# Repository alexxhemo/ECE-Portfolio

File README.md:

# Engineering Portfolio — Alexander Xhemo

This repository contains a collection of my engineering and software projects across hardware design, embedded systems, VLSI, C/C++/Python development, Linux systems programming, and full-stack web development.

The goal of this portfolio is to show the range of projects I have worked on, including circuit design, PCB layout, microcontroller programming, digital/VLSI design, backend/frontend development, and algorithmic software projects.

---

## Portfolio Areas

### PCB Design

This section includes PCB design projects involving schematic capture, component selection, board layout, routing, and manufacturing outputs.

Projects include:

- Optical transceiver PCB
- Audio amplifier PCB
- Schematic and layout documentation
- Gerber/manufacturing files where applicable
- Design screenshots and project notes

Tools used:

- Altium Designer
- KiCad
- Circuit simulation tools
- PCB layout and routing workflows

Large generated simulation files, such as `.raw` files, are intentionally excluded from the repository to keep the project clean and lightweight.

---

### VLSI Layouts and Schematics

This section contains VLSI design work, including transistor-level schematics, layouts, and timing analysis.

Projects include:

- Static master-slave register
- Full adder schematic and layout
- Sequential arithmetic circuit integration
- DRC and LVS verification work
- Setup time, hold time, and clock-to-Q delay analysis

Tools and concepts used:

- Cadence Virtuoso
- CMOS transistor-level design
- Layout design with shared diffusion
- DRC/LVS debugging
- Timing measurements and waveform analysis

---

### Microcontroller Embedded C

This section includes embedded C projects developed for microcontroller-based systems.

Projects include:

- Microcontroller I/O control
- UART/USART communication
- SPI and I2C peripheral communication
- ADC and DAC usage
- PWM control
- RTC-based timing
- State-machine-based embedded logic

Tools and platforms used:

- Microchip Studio
- AVR microcontrollers
- Embedded C
- Oscilloscope and hardware debugging
- Serial communication debugging

---

### Linear Regression Visualizer

This project is a C++ and Python-based linear regression visualizer used to demonstrate regression modeling, error calculation, and data visualization.

Main features:

- Linear regression model calculation
- Visualization of regression line and data points
- Error metric calculation
- Clean project structure for experimenting with regression behavior
- Backend logic for handling model calculations

Languages and tools used:

- C++
- Python
- Data visualization libraries
- Object-oriented programming concepts

---

### CPU Scheduler for Ubuntu

This project implements a CPU scheduling calculator and simulator for Linux/Ubuntu.

Implemented scheduling algorithms include:

- First-Come, First-Served
- Shortest Job First
- Round Robin
- Priority Scheduling

The project calculates and displays scheduling metrics such as:

- Waiting time
- Turnaround time
- Completion time
- Average performance metrics

Tools and concepts used:

- C/C++
- Ubuntu/Linux environment
- Process scheduling concepts
- Command-line compilation and testing

---

### Full-Stack Web Applications

This section includes two full-stack web applications involving frontend development, backend/API integration, authentication, database interaction, and team collaboration.

Project work includes:

- Frontend page development
- Responsive user interface design
- Backend API integration
- User authentication flows
- Database-backed application logic
- Team collaboration using GitHub, Trello, and Discord

Technologies used across these projects include:

- React
- JavaScript
- Flask / backend APIs
- SQLite
- AWS Lambda
- Auth0
- GitHub Actions / CI workflows
- Docker

---

## Skills Demonstrated

This portfolio demonstrates experience in:

- PCB schematic capture and board layout
- VLSI schematic and physical layout design
- Embedded C programming
- Microcontroller peripheral configuration
- C++ and Python application development
- Linux-based development
- CPU scheduling algorithms
- Full-stack web application development
- Git and GitHub version control
- Debugging hardware, software, and integration issues
- Technical documentation and project organization

---

## Repository Organization

The repository is organized by project category:

```text
ECE-Portfolio/
│
├── PCB Design/
│   ├── Optical Transceiver/
│   └── Audio Amplifier/
│
├── VLSI/
│   ├── Layouts/
│   ├── Schematics/
│   └── Timing Analysis/
│
├── Microcontroller Embedded C/
│
├── Linear Regression Visualizer/
│
├── CPU Scheduler Ubuntu/
│
├── Full Stack Web Apps/
│
└── README.md

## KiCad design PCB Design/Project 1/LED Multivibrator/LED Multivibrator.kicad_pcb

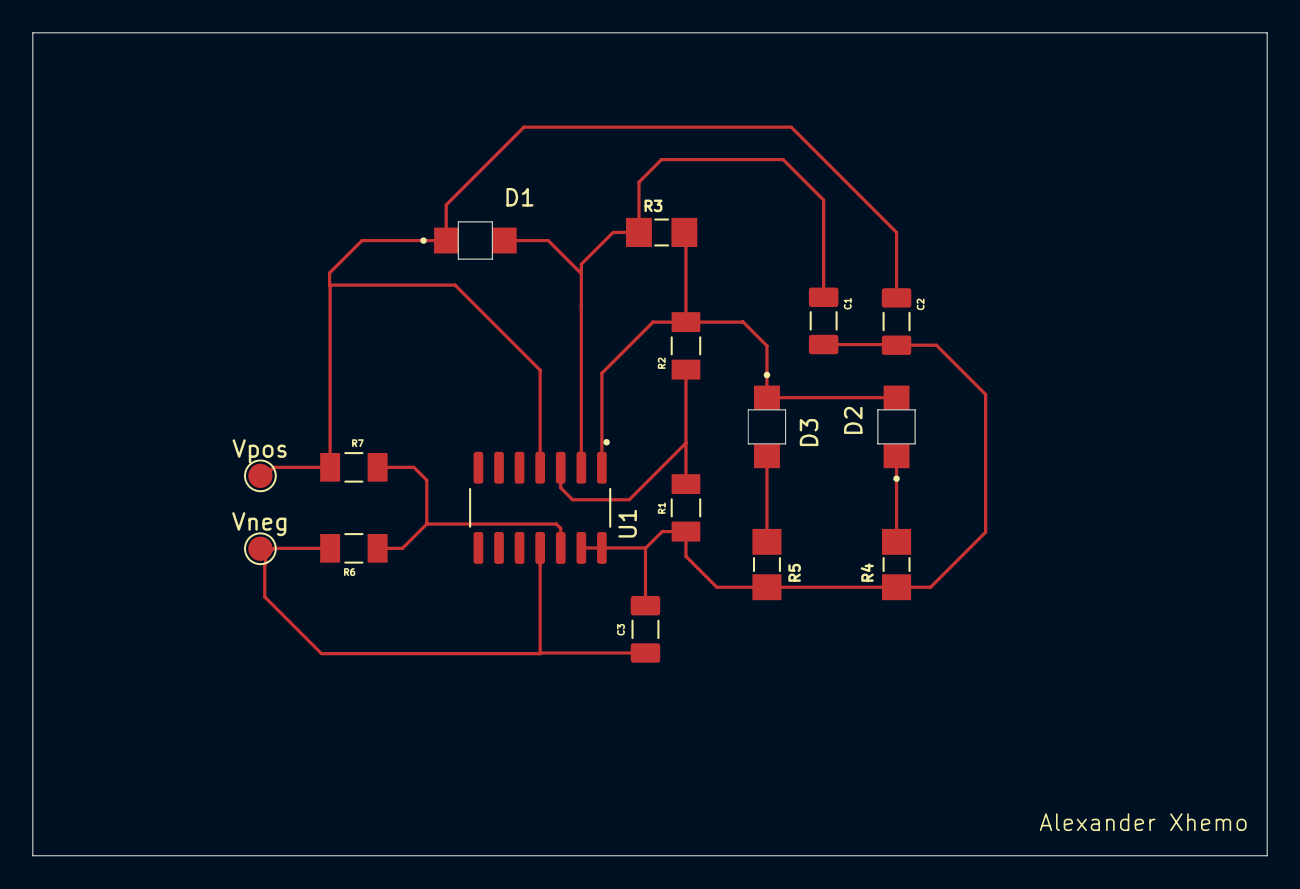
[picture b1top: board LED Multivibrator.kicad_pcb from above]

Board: 2 copper layers, 76.2 x 50.8 mm, 16 parts (0 on the bottom side), 9 nets.

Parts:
C1, C2, C3: CL31B106KAHNNNE; CAPC3216X180N
D1, D2, D3: LTST-C230KRKT; LED_LTST-C230KRKT
R1, R2, R6, R7: 1k; RESC3216X70N
R3: 20k; RESC3216X65
R4, R5: 330; RESC3216X65
U1: LM324DR; SOIC127P600X175-14N
Vneg: TestPoint; TestPoint_Pad_D1.5mm
Vpos: TestPoint; TestPoint_Pad_D1.5mm

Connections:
+4.5: C2.1, D1.C, R7.1, U1.4 (VCC), Vpos.1
-4.5V: C3.1, R6.2, U1.11 (GND), Vneg.1
GND: C1.2, C2.2, C3.2, R1.1, R4.2, R5.2, U1.13 (4IN-), U1.14 (4OUT)
unnamed: D2.C, R4.1
unnamed: D3.A, R5.1
unnamed: R1.2, R2.1, U1.3 (1IN+)
unnamed: C1.1, D1.A, R3.1, U1.2 (1IN-)
unnamed: D2.A, D3.C, R2.2, R3.2, U1.1 (1OUT)
unnamed: R6.1, R7.2, U1.12 (4IN+)

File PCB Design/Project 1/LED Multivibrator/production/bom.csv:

Designator,Footprint,Quantity,Value,LCSC Part #
"C1, C2, C3",CAPC3216X180N,3,CL31B106KAHNNNE,
"D1, D2, D3",LED_LTST-C230KRKT,3,LTST-C230KRKT,
"R1, R2, R6, R7",RESC3216X70N,4,1k,
R3,RESC3216X65,1,20k,
"R4, R5",RESC3216X65,2,330,
U1,SOIC127P600X175-14N,1,LM324DR,
"VNEG, VPOS",TestPoint_Pad_D1.5mm,2,TestPoint,

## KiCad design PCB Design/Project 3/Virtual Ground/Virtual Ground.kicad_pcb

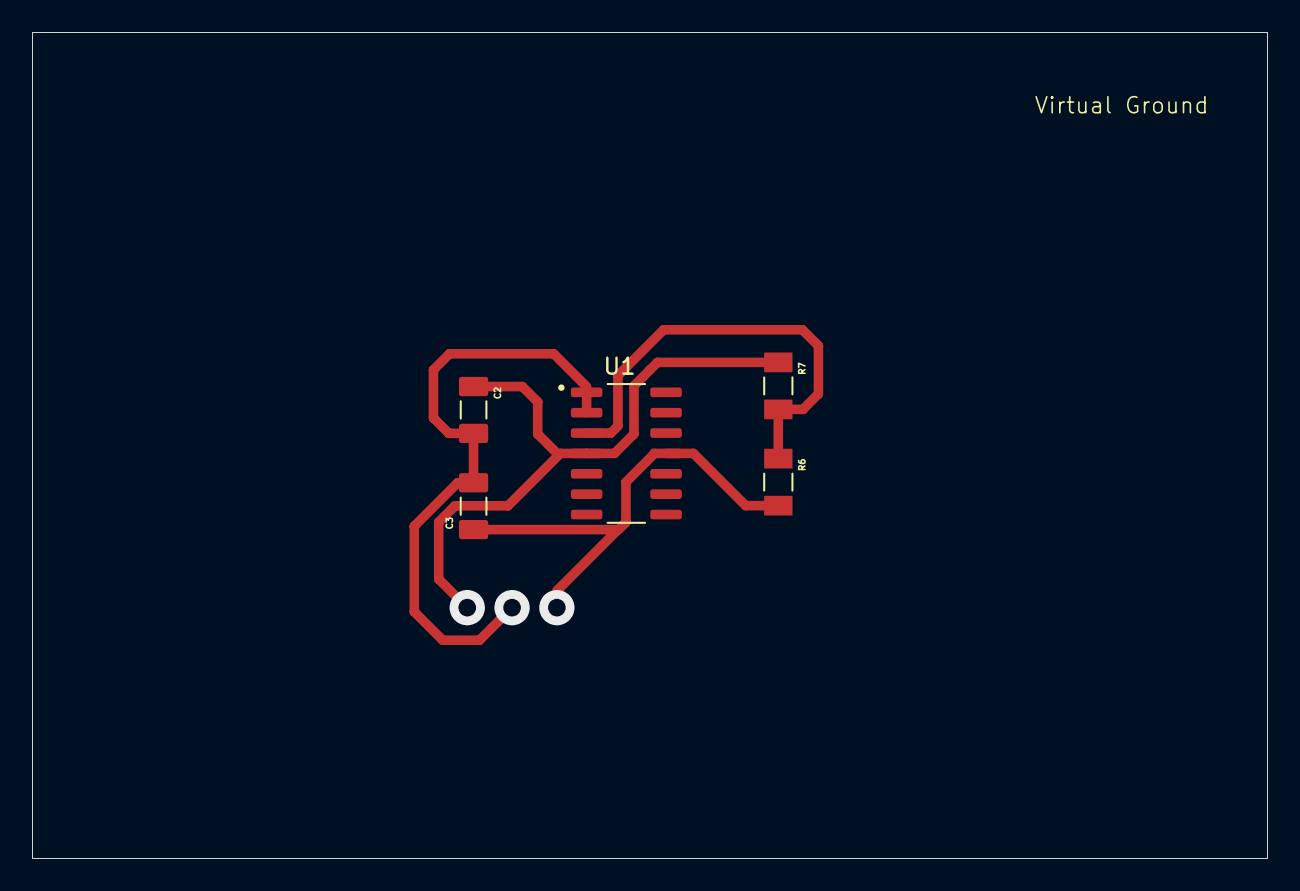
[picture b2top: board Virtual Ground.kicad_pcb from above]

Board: 2 copper layers, 77.0 x 51.5 mm, 5 parts (0 on the bottom side), 4 nets.

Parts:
C2, C3: CL31B106KAHNNNE; CAPC3216X180N
R6, R7: 1k; RESC3216X70N
U1: LM324DR; SOIC127P600X175-14N

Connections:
/V+: C2.1, R7.1, U1.4 (VCC)
/V-: C3.1, R6.2, U1.11 (GND)
/Virtual_Ground: C2.2, C3.2, U1.1 (1OUT), U1.2 (1IN-)
unnamed: R6.1, R7.2, U1.3 (1IN+)

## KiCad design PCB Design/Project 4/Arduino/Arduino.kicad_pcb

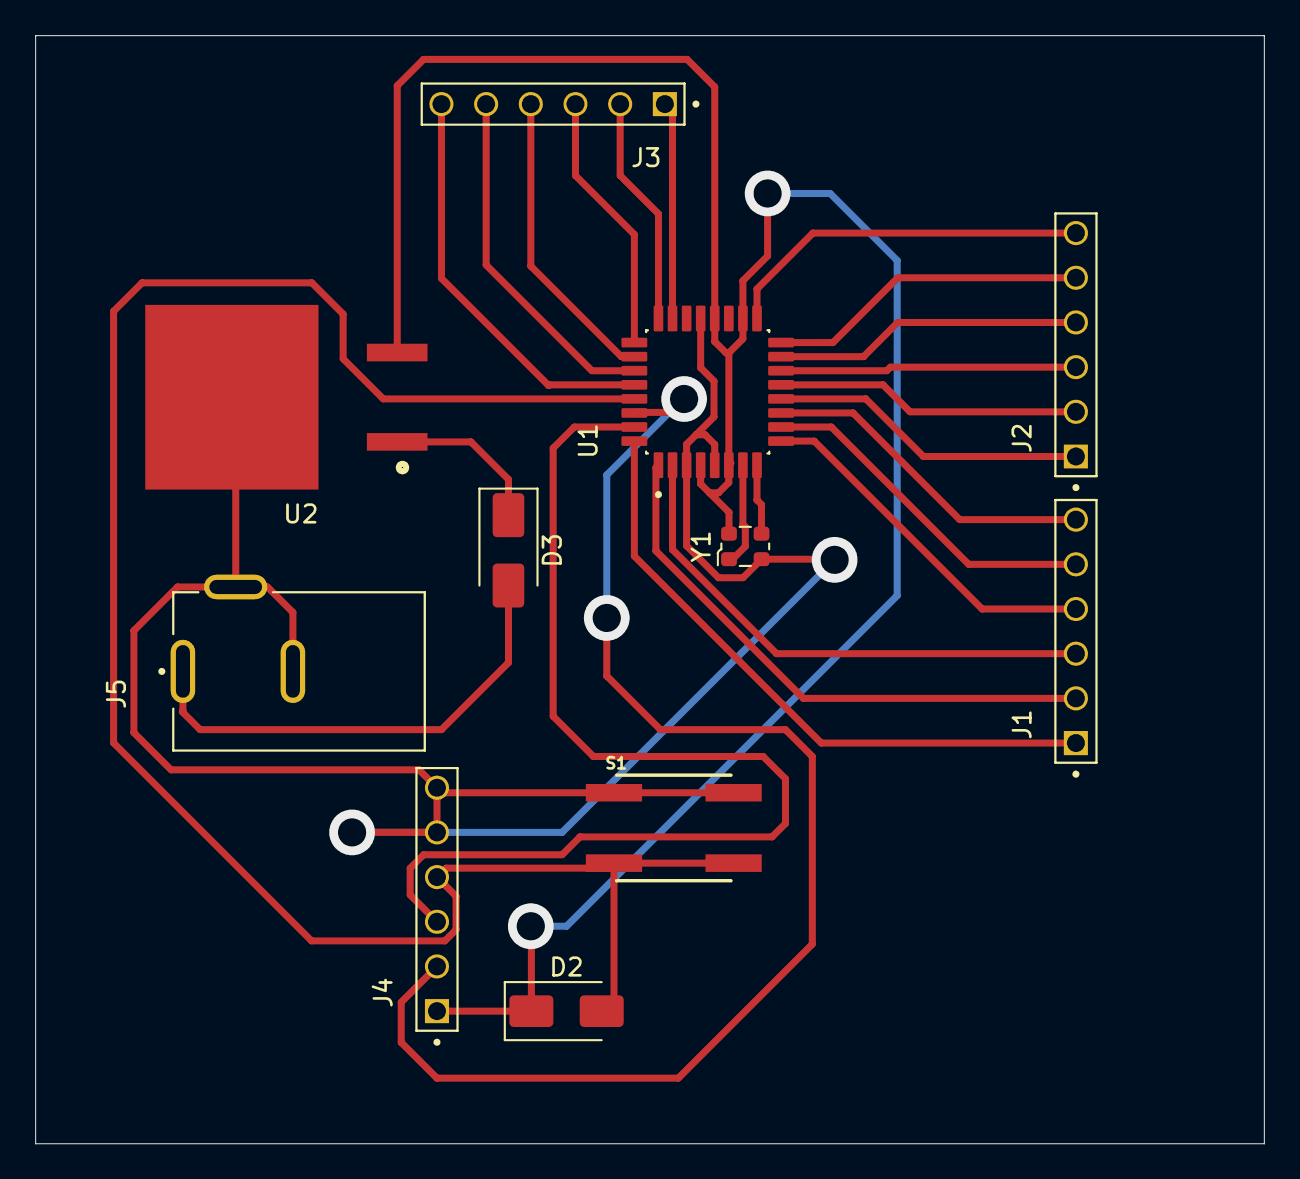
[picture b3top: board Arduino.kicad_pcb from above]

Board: 2 copper layers, 69.8 x 63.0 mm, 11 parts (0 on the bottom side), 27 nets.

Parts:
D2, D3: MRA4007T3G; D_SMA
J1, J2, J3, J4: 3-644456-6; TE_3-644456-6
J5: 54-00166; TENSILITY_54-00166
S1: EVQ-Q2B02W; SW_EVQ-Q2B02W
U1: ATMEGA328P-AU; QFP80P900X900X120-32N
U2: L7805ACD2T-TR; TO254P1515X470-3N
Y1: ECS-2520MV-xxx-xx; Oscillator_SMD_ECS_2520MV-xxx-xx-4Pin_2.5x2.0mm

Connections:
/LED: J2.6, U1.17 (PB5)
/MISO: J2.5, U1.16 (PB4)
/MOSI: J2.4, U1.15 (PB3)
/PB0: J2.1, U1.12 (PB0)
/PB1: J2.2, U1.13 (PB1)
/PB2: J2.3, U1.14 (PB2)
/PC0: J3.1, U1.23 (PC0)
/PC1: J3.2, U1.24 (PC1)
/PC2: J3.3, U1.25 (PC2)
/PC3: J3.4, U1.26 (PC3)
/PD2: J1.1, U1.32 (PD2)
/PD3: J1.2, U1.1 (PD3)
/PD4: J1.3, U1.2 (PD4)
/PD5: J1.4, U1.9 (PD5)
/PD6: J1.5, U1.10 (PD6)
/PD7: J1.6, U1.11 (PD7)
/RST: D2.2 (A), J4.4, S1.A, S1.A', U1.29 (PC6/~RESET)
/RX: J4.2, U1.30 (PD0)
/SCL: J3.6, U1.28 (PC5)
/SDA: J3.5, U1.27 (PC4)
/TX: J4.3, U1.31 (PD1)
GND: J4.5, J4.6, J5.B, J5.C, S1.B, S1.B', U1.3 (GND), U1.5 (GND__1), U1.21 (GND__2), U2.3 (GND), Y1.2 (GND)
unnamed: D2.1 (K), J4.1, U1.4 (VCC), U1.6 (VCC__1), U1.18 (AVCC), U1.20 (AREF), U2.2 (OUT), Y1.4 (VDD)
unnamed: D3.2 (A), J5.A
unnamed: D3.1 (K), U2.1 (IN)
unnamed: U1.7 (PB6), Y1.1 (Tri-State)
unnamed: U1.8 (PB7), Y1.3 (OUT)

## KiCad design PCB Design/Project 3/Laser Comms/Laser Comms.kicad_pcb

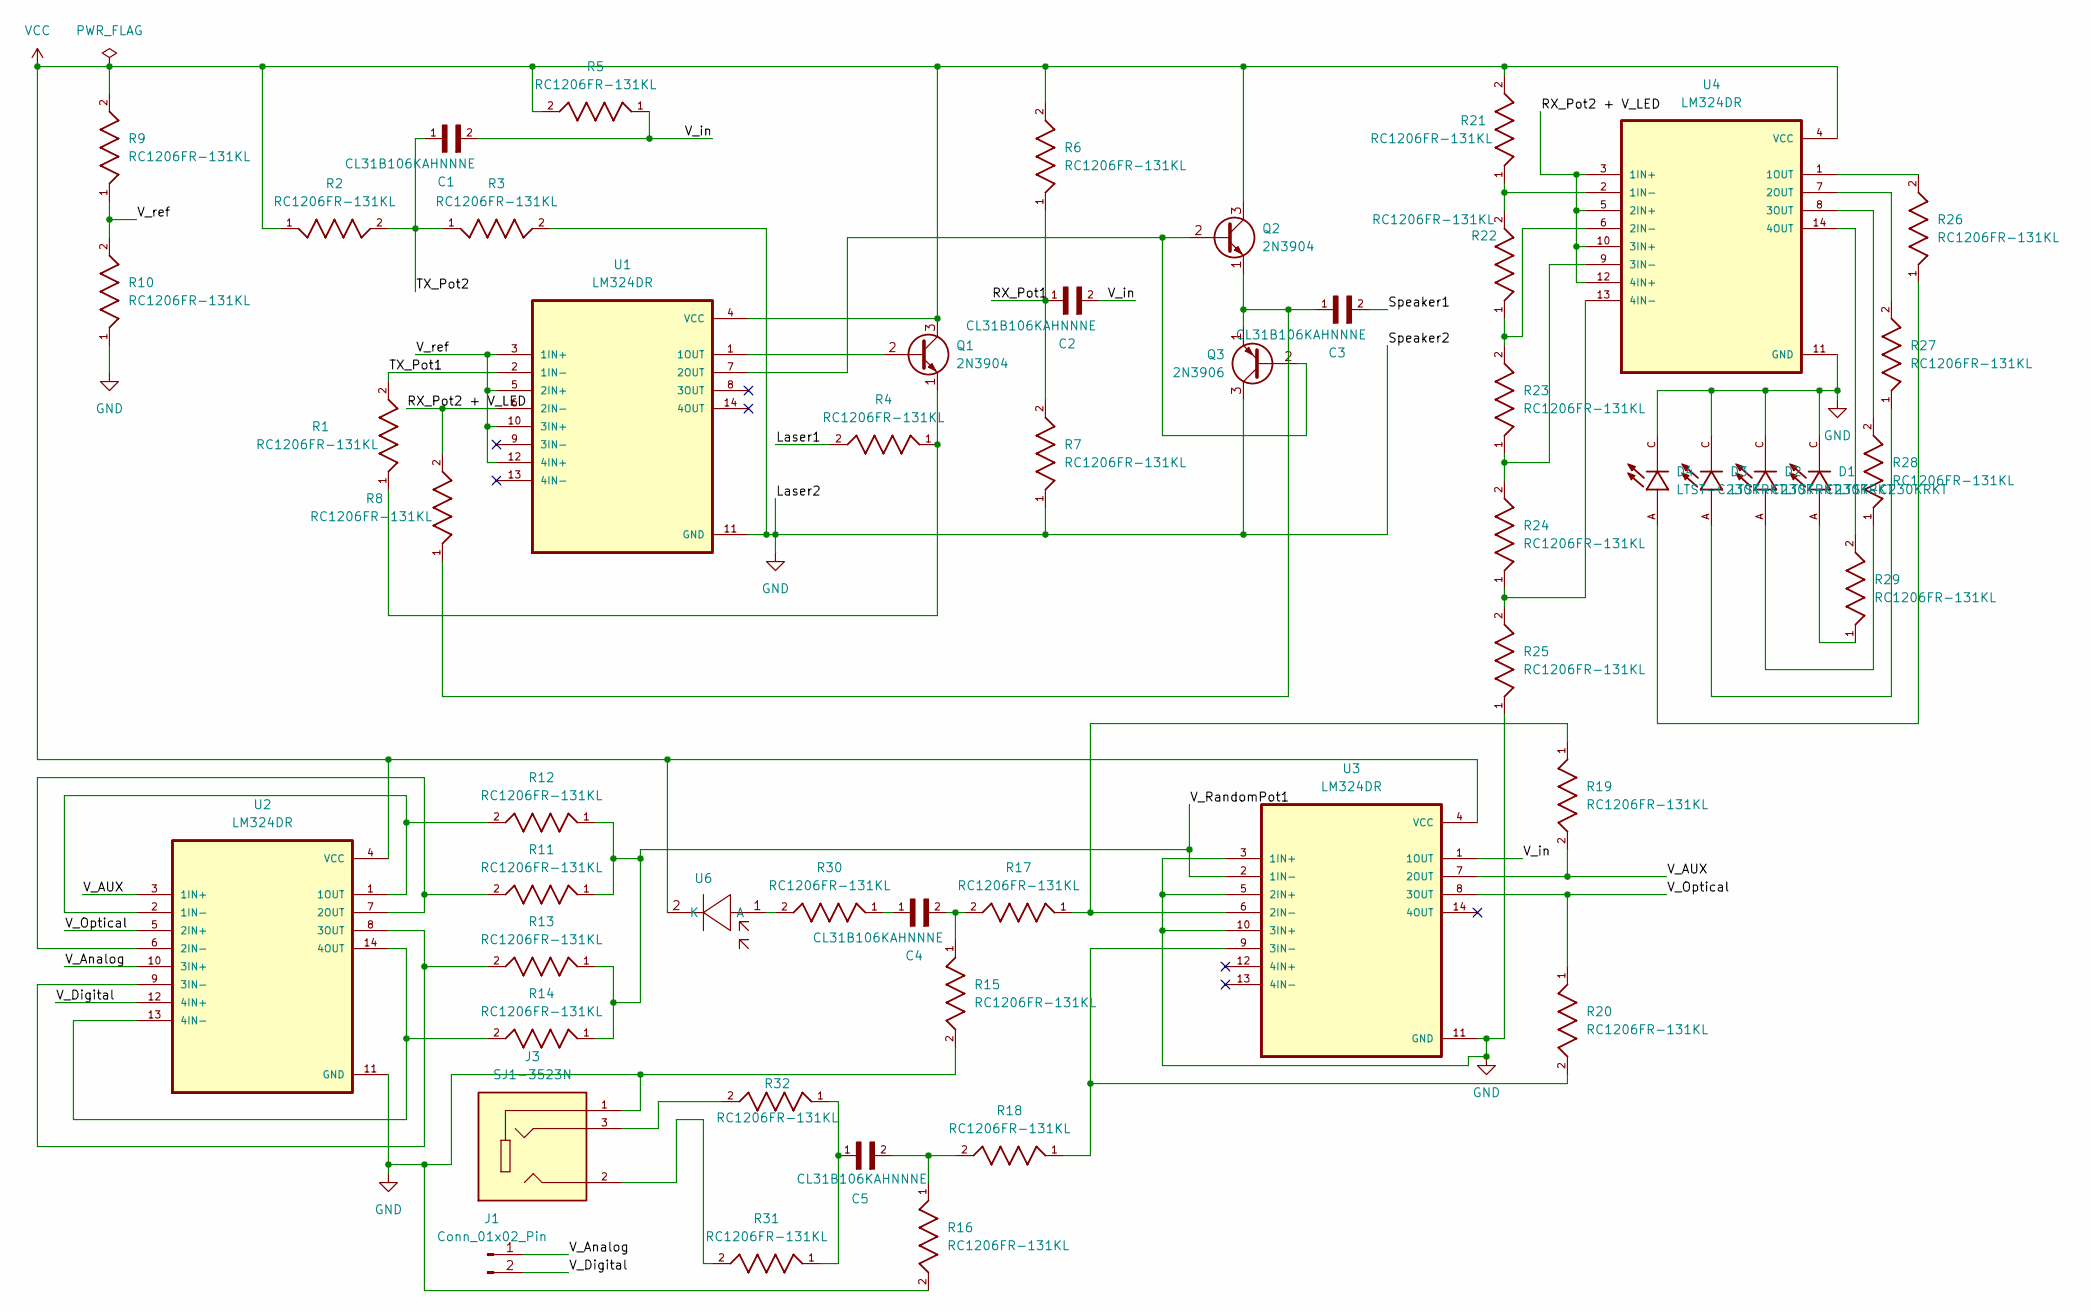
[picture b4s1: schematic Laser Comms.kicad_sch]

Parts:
C1, C2, C3, C4, C5: CL31B106KAHNNNE; CAPC3216X180N
D1, D2, D3, D4: LTST-C230KRKT; LED_LTST-C230KRKT; PARTREV E
J1: Conn_01x02_Pin
J3: SJ1-3523N; CUI_SJ1-3523N; PARTREV 1.05
Q1, Q2: 2N3904; TO-92_Inline
Q3: 2N3906; TO-92_Inline
R1, R2, R3, R4, R5, R6, R7, R8, R9, R10, R11, R12, R13, R14, R15, R16, R17, R18, R19, R20, R21, R22, R23, R24, R25, R26, R27, R28, R29, R30, R31, R32: RC1206FR-131KL; RESC3216X65
U1, U2, U3, U4: LM324DR; SOIC127P600X175-14N
U6: PhotoDiode

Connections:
/Laser1: R4.2
/RX_Pot1: C2.1, R6.1, R7.2
/RX_Pot2 + V_LED: R8.2, U1.6 (2IN-), U4.3 (1IN+), U4.5 (2IN+), U4.10 (3IN+), U4.12 (4IN+)
/Speaker1: C3.2
/TX_Pot1: R1.2, U1.2 (1IN-)
/TX_Pot2: C1.1, R2.2, R3.1
/V_AUX: R19.2, U2.3 (1IN+), U3.7 (2OUT)
/V_Analog: J1.1, U2.10 (3IN+)
/V_Digital: J1.2, U2.12 (4IN+)
/V_Optical: R20.1, U2.5 (2IN+), U3.8 (3OUT)
/V_RandomPot1: R11.1, R12.1, R13.1, R14.1, U3.2 (1IN-)
/V_in: C1.2, C2.2, R5.1, U3.1 (1OUT)
/V_ref: R9.1, R10.2, U1.3 (1IN+), U1.5 (2IN+), U1.10 (3IN+), U1.12 (4IN+)
GND: D1.C, D2.C, D3.C, D4.C, J3.1, Q3.3 (C), R3.2, R7.1, R10.1, R15.2, R16.2, R25.1, U1.11 (GND), U2.11 (GND), U3.3 (1IN+), U3.5 (2IN+), U3.10 (3IN+), U3.11 (GND), U4.11 (GND)
unnamed: C4.1, R30.1
unnamed: C4.2, R15.1, R17.2
unnamed: C5.1, R31.1, R32.1
unnamed: C5.2, R16.1, R18.2
unnamed: D1.A, R29.1
unnamed: D2.A, R28.1
unnamed: D3.A, R27.1
unnamed: D4.A, R26.1
unnamed: J3.2, R31.2
unnamed: J3.3, R32.2
unnamed: Q1.2 (B), U1.1 (1OUT)
unnamed: Q1.1 (E), R1.1, R4.1
unnamed: Q2.2 (B), Q3.2 (B), U1.7 (2OUT)
unnamed: C3.1, Q2.1 (E), Q3.1 (E), R8.1
unnamed: R12.2, U2.1 (1OUT), U2.2 (1IN-)
unnamed: R11.2, U2.6 (2IN-), U2.7 (2OUT)
unnamed: R13.2, U2.8 (3OUT), U2.9 (3IN-)
unnamed: R14.2, U2.13 (4IN-), U2.14 (4OUT)
unnamed: R17.1, R19.1, U3.6 (2IN-)
unnamed: R18.1, R20.2, U3.9 (3IN-)
unnamed: R21.1, R22.2, U4.2 (1IN-)
unnamed: R26.2, U4.1 (1OUT)
unnamed: R22.1, R23.2, U4.6 (2IN-)
unnamed: R27.2, U4.7 (2OUT)
unnamed: R23.1, R24.2, U4.9 (3IN-)
unnamed: R28.2, U4.8 (3OUT)
unnamed: R24.1, R25.2, U4.13 (4IN-)
unnamed: R29.2, U4.14 (4OUT)
unnamed: R30.2, U6.1 (A)
VCC: Q1.3 (C), Q2.3 (C), R2.1, R5.2, R6.2, R9.2, R21.2, U1.4 (VCC), U2.4 (VCC), U3.4 (VCC), U4.4 (VCC), U6.2 (K)

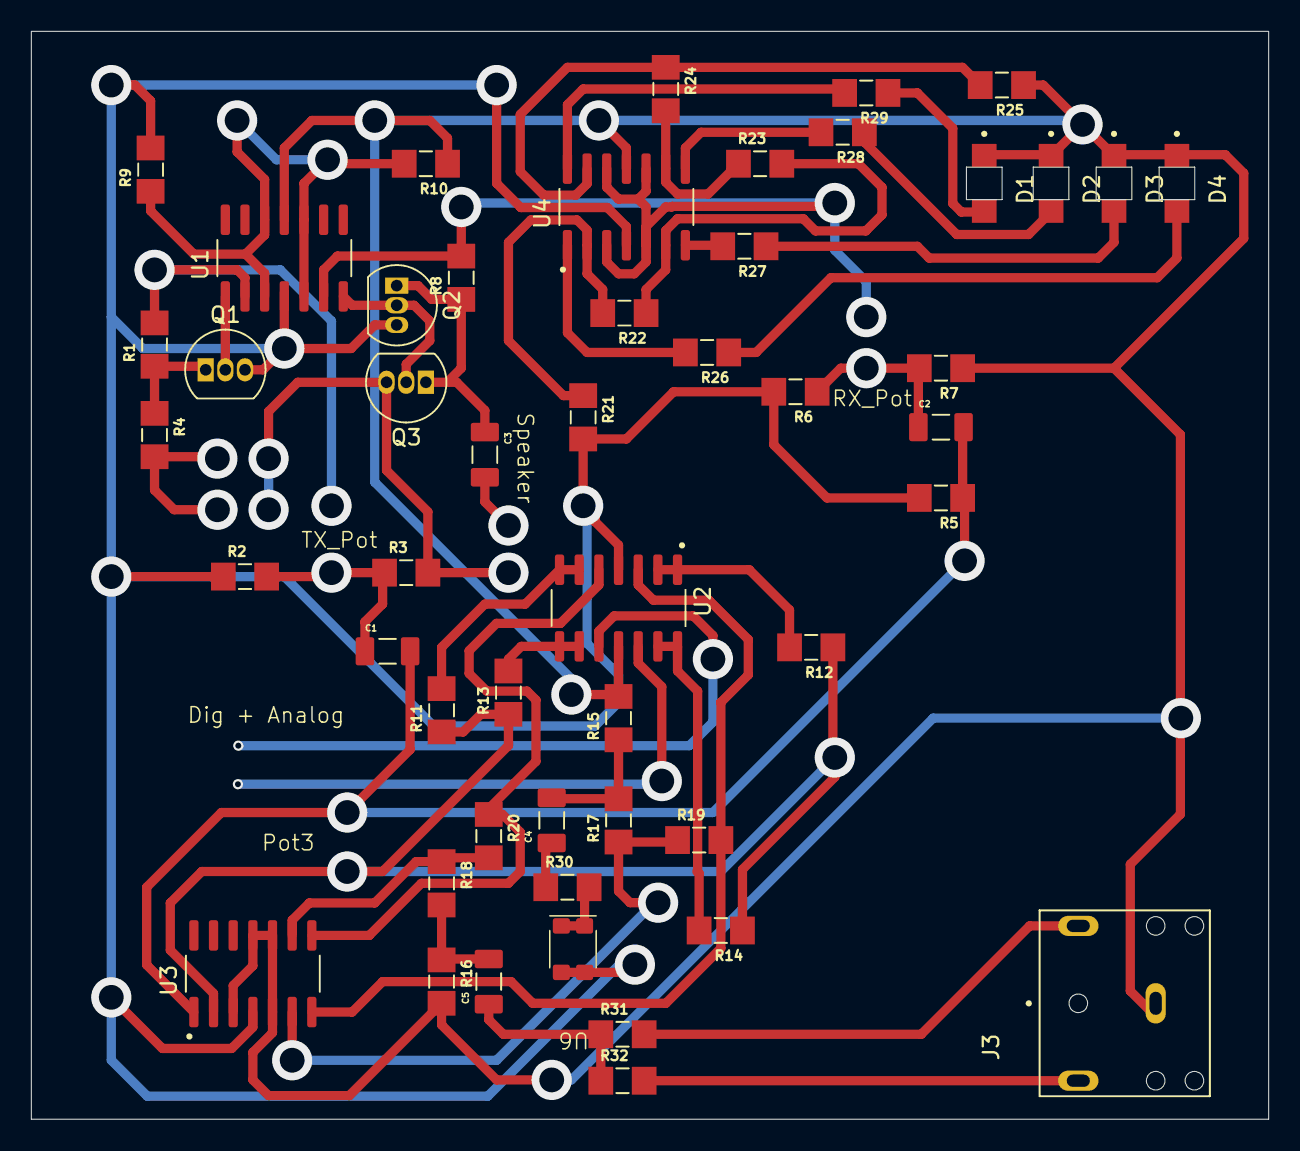
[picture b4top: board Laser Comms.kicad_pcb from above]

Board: 2 copper layers, 79.9 x 70.3 mm, 50 parts (0 on the bottom side), 40 nets.

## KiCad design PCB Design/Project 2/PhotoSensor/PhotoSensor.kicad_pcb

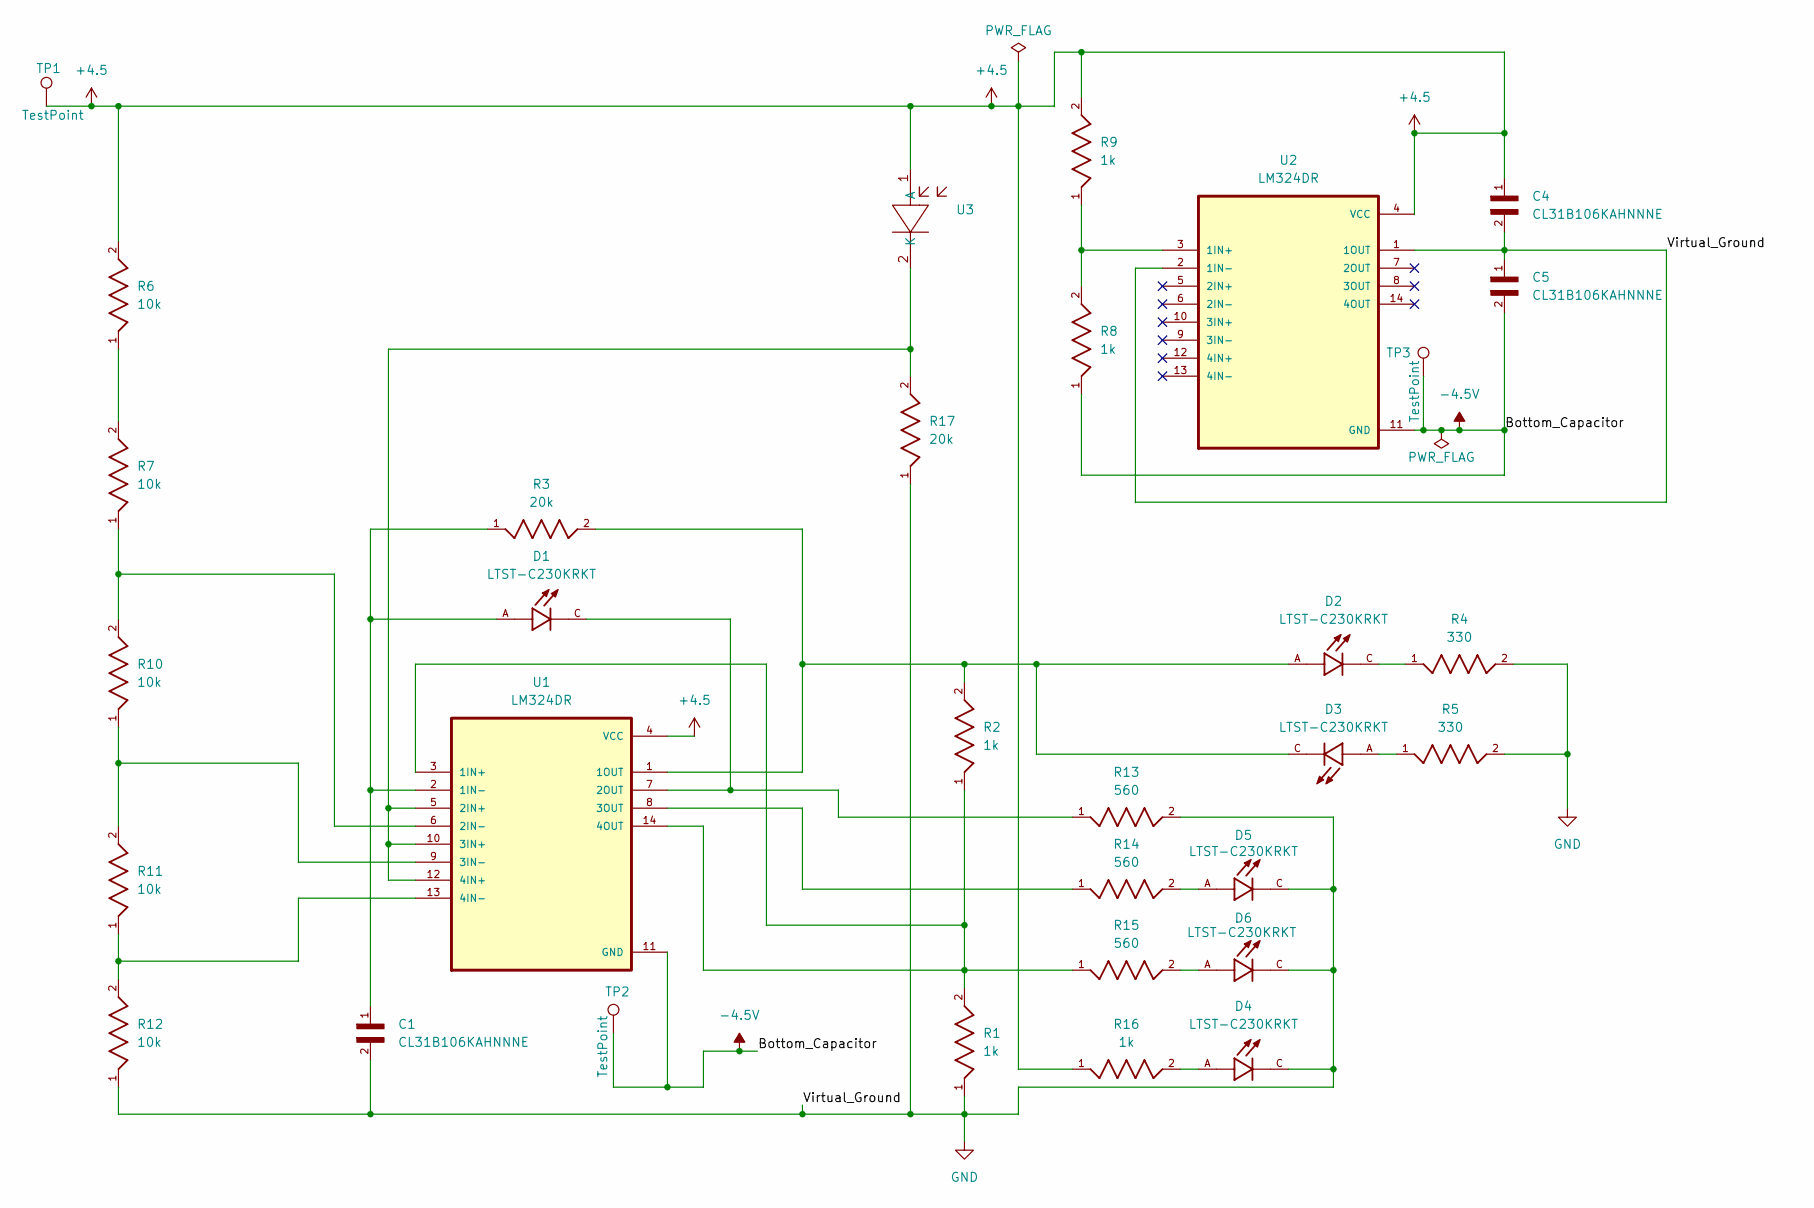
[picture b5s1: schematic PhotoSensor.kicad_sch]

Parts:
C1, C4, C5: CL31B106KAHNNNE; CAPC3216X180N
D1, D2, D3, D4, D5, D6: LTST-C230KRKT; LED_LTST-C230KRKT; PARTREV E
R1, R2, R8, R9, R16: 1k; RESC3216X65
R3, R17: 20k; RESC3216X65
R4, R5: 330; RESC3216X65
R6, R7, R10, R11, R12: 10k; RESC3216X65
R13, R14, R15: 560; RESC3216X65
TP1, TP2, TP3: TestPoint; TestPoint_Pad_D1.5mm
U1, U2: LM324DR; SOIC127P600X175-14N
U3: PhotoDiode

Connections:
+4.5: C4.1, R6.2, R9.2, R16.1, TP1.1, U1.4 (VCC), U2.4 (VCC), U3.1 (A)
-4.5V: C5.2, R8.1, TP2.1, TP3.1, U1.11 (GND), U2.11 (GND)
GND: C1.2, C4.2, C5.1, D4.C, D5.C, D6.C, R1.1, R4.2, R5.2, R12.1, R13.2, R17.1, U2.1 (1OUT), U2.2 (1IN-)
unnamed: D2.C, R4.1
unnamed: D3.A, R5.1
unnamed: D4.A, R16.2
unnamed: D5.A, R14.2
unnamed: D6.A, R15.2
unnamed: R6.1, R7.2
unnamed: R1.2, R2.1, R15.1, U1.3 (1IN+), U1.14 (4OUT)
unnamed: C1.1, D1.A, R3.1, U1.2 (1IN-)
unnamed: D2.A, D3.C, R2.2, R3.2, U1.1 (1OUT)
unnamed: R17.2, U1.5 (2IN+), U1.10 (3IN+), U1.12 (4IN+), U3.2 (K)
unnamed: R7.1, R10.2, U1.6 (2IN-)
unnamed: D1.C, R13.1, U1.7 (2OUT)
unnamed: R10.1, R11.2, U1.9 (3IN-)
unnamed: R14.1, U1.8 (3OUT)
unnamed: R11.1, R12.2, U1.13 (4IN-)
unnamed: R8.2, R9.1, U2.3 (1IN+)

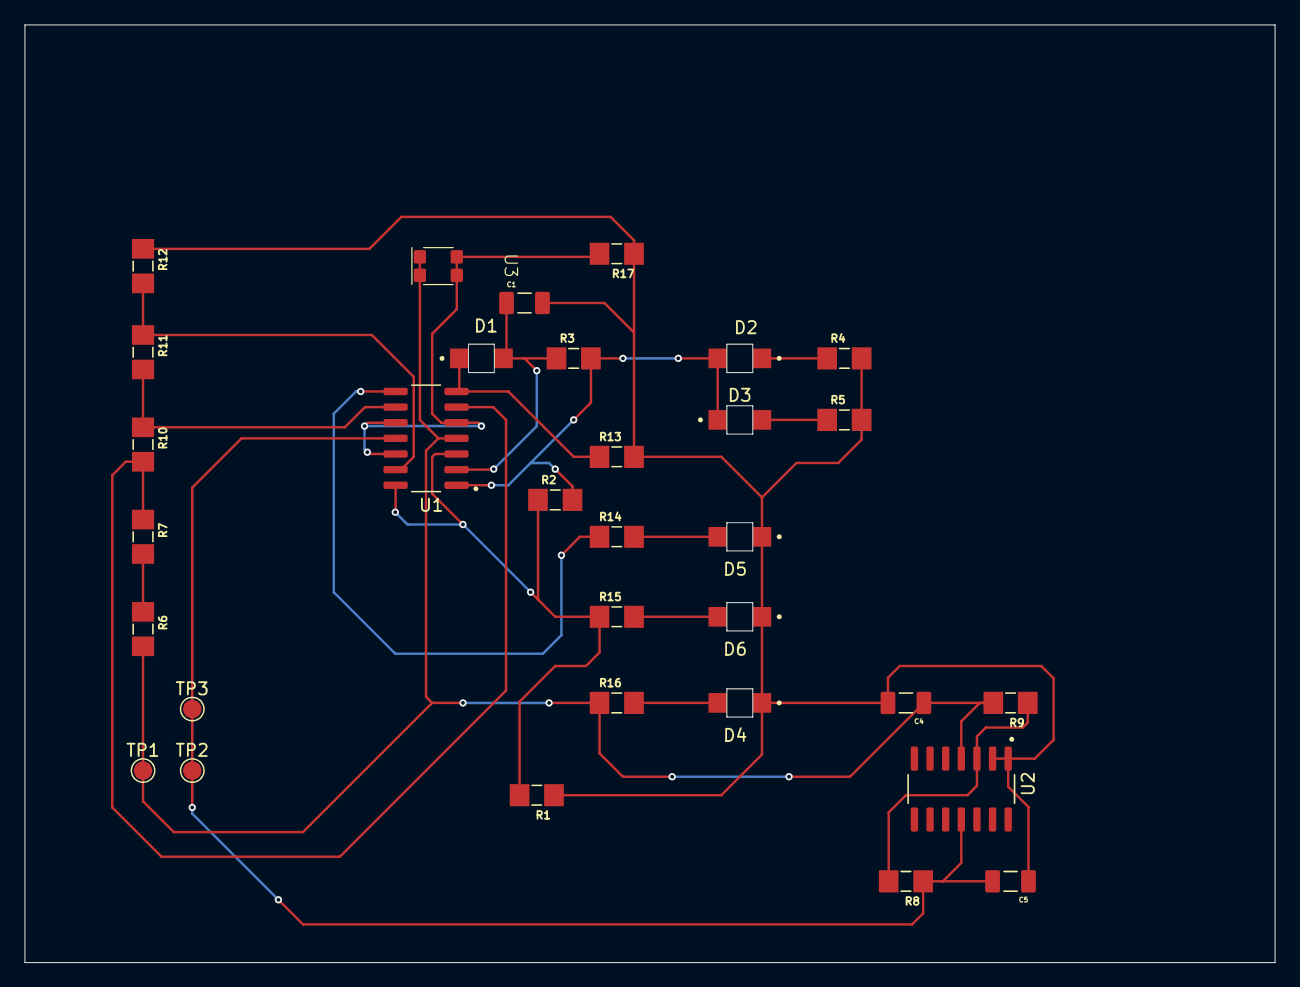
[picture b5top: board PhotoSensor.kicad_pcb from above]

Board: 2 copper layers, 101.6 x 76.2 mm, 32 parts (0 on the bottom side), 19 nets.

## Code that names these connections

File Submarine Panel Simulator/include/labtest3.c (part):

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 * Note: TCA0 is configured in SINGLESLOPE mode in main.c for PWM capability
 */
static void init_pwm_c1(void) {
  // Route TCA0 to PORTC: WO0→PC0, WO1→PC1, WO2→PC2
  PORTMUX.TCAROUTEA =
      (PORTMUX.TCAROUTEA & ~PORTMUX_TCA0_gm) | PORTMUX_TCA0_PORTC_gc;

  // Set PC1 as output
  PORTC.DIRSET = PIN1_bm;

  // Enable Compare Channel 1 output (WO1)
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}

static void led_mode_chase(void) {
  // Night rider chase effect on PORTD (skipping PD6 which is DAC output)
  // Valid LEDs: PD0, PD1, PD2, PD3, PD4, PD5, PD7 (7 LEDs total)
  static uint32_t last_chase_update_ms = 0;
  uint32_t current_ms = labtest3_ms_counter;

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                                          4, 5, 7}; // Skip pin 6 (DAC)
    static uint8_t chase_index = 0;

    PORTD.OUTCLR = 0b10111111;                     // Clear all LEDs except PD6
    PORTD.OUTSET = (1 << chase_pins[chase_index]); // Set current LED

    chase_index = (chase_index + 1) % 7; // Cycle through 7 LEDs
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//================================

static void init_buttons(void) {
  // Configure PB5 and PB2 as inputs with pull-ups (no interrupts to avoid
  // freezing)
  PORTB.DIRCLR = PIN5_bm | PIN2_bm;
  PORTB.PIN5CTRL = PORT_PULLUPEN_bm;
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      pb2_pressed = false;
    }

    // PB5 freeze toggle (only if PB2 not pressed)
    if (pb5_current && !pb5_last && !pb2_current) {
      led_mode_frozen = !led_mode_frozen;
      if (led_mode_frozen) {
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      }
    }

    // PB2 sweep toggle (only if PB5 not pressed)
    if (pb2_current && !pb2_last && !pb5_current) {
      sweep_mode_active = !sweep_mode_active;
      sweep_time_ms = 0;
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
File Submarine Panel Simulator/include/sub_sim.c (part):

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// Pin Assignments (AVR128DB48)
//================================
// Circuit Breaker Buttons (Active Low with Pull-ups)
#define BTN_SYS_RESET_PIN PIN2_bm   // PB2 (already configured in main.c)
#define BTN_O2_CB_PIN PIN3_bm       // PC3
#define BTN_RX_CB_PIN PIN4_bm       // PC4
#define BTN_REACTOR_PWR_PIN PIN5_bm // PC5
#define BTN_MAIN_BKR_PIN PIN2_bm    // PC2

// LED Y-Pattern (Active High)
#define LED_TOP_RIGHT_PIN PIN0_bm  // PD0 Yellow - Air Quality
#define LED_TOP_LEFT_PIN PIN1_bm   // PD1 Blue - Torpedo Inbound
#define LED_BOT_TOP_RIGHT PIN2_bm  // PD2 Red - Backup O2 In Service
#define LED_BOT_TOP_LEFT PIN3_bm   // PD3 Red - Primary O2 In Service
#define LED_TOP_CENTER_PIN PIN4_bm // PD4 White - Reactor Main Power
#define LED_BOT_CENTER_PIN PIN5_bm // PD5 Green - Reactor Status

/*
    Master Potentiometer
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
void sub_sim_init(void) {
  // Configure button inputs (active low with pull-ups) on PORTC
  // PC3, PC4, PC5, PC2
  PORTC.DIRCLR =
      BTN_O2_CB_PIN | BTN_RX_CB_PIN | BTN_REACTOR_PWR_PIN | BTN_MAIN_BKR_PIN;
  PORTC.PIN3CTRL = PORT_PULLUPEN_bm;
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    flash_state = !flash_state;

    // --- Air Quality / Low O2 Logic ---
    // PD0 (Air Quality)
    // Flash if: Low O2 Event Active
    // Note: Removed gas_alarm check to prevent flashing before event

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    }

    // --- Torpedo Logic ---
    // PD1 (Torpedo)
    // Flash if Torpedo Event Active
    bool torp_running = false;
    if ((current_state == DIVE_PHASE_25 && phase_events[0] == EVENT_TORPEDO &&
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    }

    // --- Reactor Logic ---
    // PD5 (Reactor Status)
    // Flash if Reactor Event Active
    bool rx_running = false;
    if ((current_state == DIVE_PHASE_25 && phase_events[0] == EVENT_REACTOR &&
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    }

    // --- O2 Scrubber Status ---
    // PD3 (Primary) vs PD2 (Backup)
    if (current_state >= DIVE_DESCENDING) {
      if (backup_o2_active) {
        PORTD.OUTSET = LED_BOT_TOP_RIGHT; // Backup ON
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      } else if (startup_step == 1) {
        if (current_tick - startup_timer > (2 * SUB_SIM_TICKS_PER_SECOND)) {
          sub_sim_lcd_print("REACTOR CRITICAL", "CLOSE MAIN BKR  ");
          // Reactor Critical: Turn ON Reactor Status LED (PD5)
          PORTD.OUTSET = LED_BOT_CENTER_PIN;
          startup_step = 2;
        }
      } else if (startup_step == 2) {
        // Wait for Main Breaker button press (PC2)
        if (sub_sim_button_main_bkr_pressed()) {
          _delay_ms(50); // Debounce

          // Turn ON Main Power LED (White - PD4)
          PORTD.OUTSET = LED_TOP_CENTER_PIN;

          // Establish Normal Lineup
          // PD0 (Air Quality) ON
          // PD1 (Torpedo) ON
          // PD3 (Primary O2) ON
          PORTD.OUTSET =
              LED_TOP_RIGHT_PIN | LED_TOP_LEFT_PIN | LED_BOT_TOP_LEFT;

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}

static void sub_sim_led_set(uint8_t pattern) {
  // Set LED pattern (bits 0-5 correspond to PD0-PD5)
  // PD0: LED_TOP_RIGHT_PIN
  // PD1: LED_TOP_LEFT_PIN
  // PD2: LED_BOT_TOP_RIGHT
  // PD3: LED_BOT_TOP_LEFT
  // PD4: LED_TOP_CENTER_PIN
  // PD5: LED_BOT_CENTER_PIN

  if (pattern & (1 << 0))
    PORTD.OUTSET = PIN0_bm;
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    if (display_toggle < 15) {
      sub_sim_lcd_print("SET DIVE TIME   ", line2);
    } else {
      sub_sim_lcd_print("PRESS RX START  ", "TO START (PC5)  ");
    }

    if (display_toggle >= 30) {
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
    // Debug: Check buttons and print to UART if pressed (to verify wiring)
    if (sub_sim_button_reactor_startup_pressed() && DEBUG)
      aos_printf("DEBUG: PC5 Pressed\r\n");
    if (sub_sim_button_o2_cb_pressed() && DEBUG)
      aos_printf("DEBUG: PC3 Pressed\r\n");
    if (sub_sim_button_rx_cb_pressed() && DEBUG)
      aos_printf("DEBUG: PC4 Pressed\r\n");
  }

  // Wait for reactor startup button
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    sub_sim_set_sound_mode(SOUND_GENERAL_ALARM);
    sub_sim_lcd_print("ALARM: LOW O2   ", "RESET O2 CB     ");
    aos_printf("\r\n[CASUALTY] LOW OXYGEN WARNING\r\n");
    aos_printf("Press O2 Circuit Breaker (PC3) within 20 seconds!\r\n");
    o2_alarm_triggered = true;
    o2_awaiting_response = true;
    phase_start_tick = current_tick;
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    sub_sim_lcd_print("RX PLANT CASUALTY", "SNORKLE!!!!     ");
    aos_printf("\r\n[CASUALTY] REACTOR PLANT CASUALTY\r\n");
    aos_printf("Reduce to periscope depth, transfer to emergency diesel\r\n");
    aos_printf("Press Reactor CB (PC4) to transfer power!\r\n");
    rx_alarm_triggered = true;
    rx_awaiting_transfer = true;
    phase_start_tick = current_tick;
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
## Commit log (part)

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2026-05-06 Create First File
2026-05-06 Farm Market Web App
2026-05-06 Added Linear Regression Visualizer
2026-05-06 CPU in VHDL
2026-05-06 Updated CPU code
2026-05-06 Microcontroller Project
2026-05-06 VLSI Designs
2026-05-06 My PCB/LTSpice/SolidWorks Designs
2026-05-06 CPU Scheduler (Ubuntu) / Snooze Streak
